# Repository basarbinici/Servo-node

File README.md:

# Servo-node
Isolated PWM generator from CAN

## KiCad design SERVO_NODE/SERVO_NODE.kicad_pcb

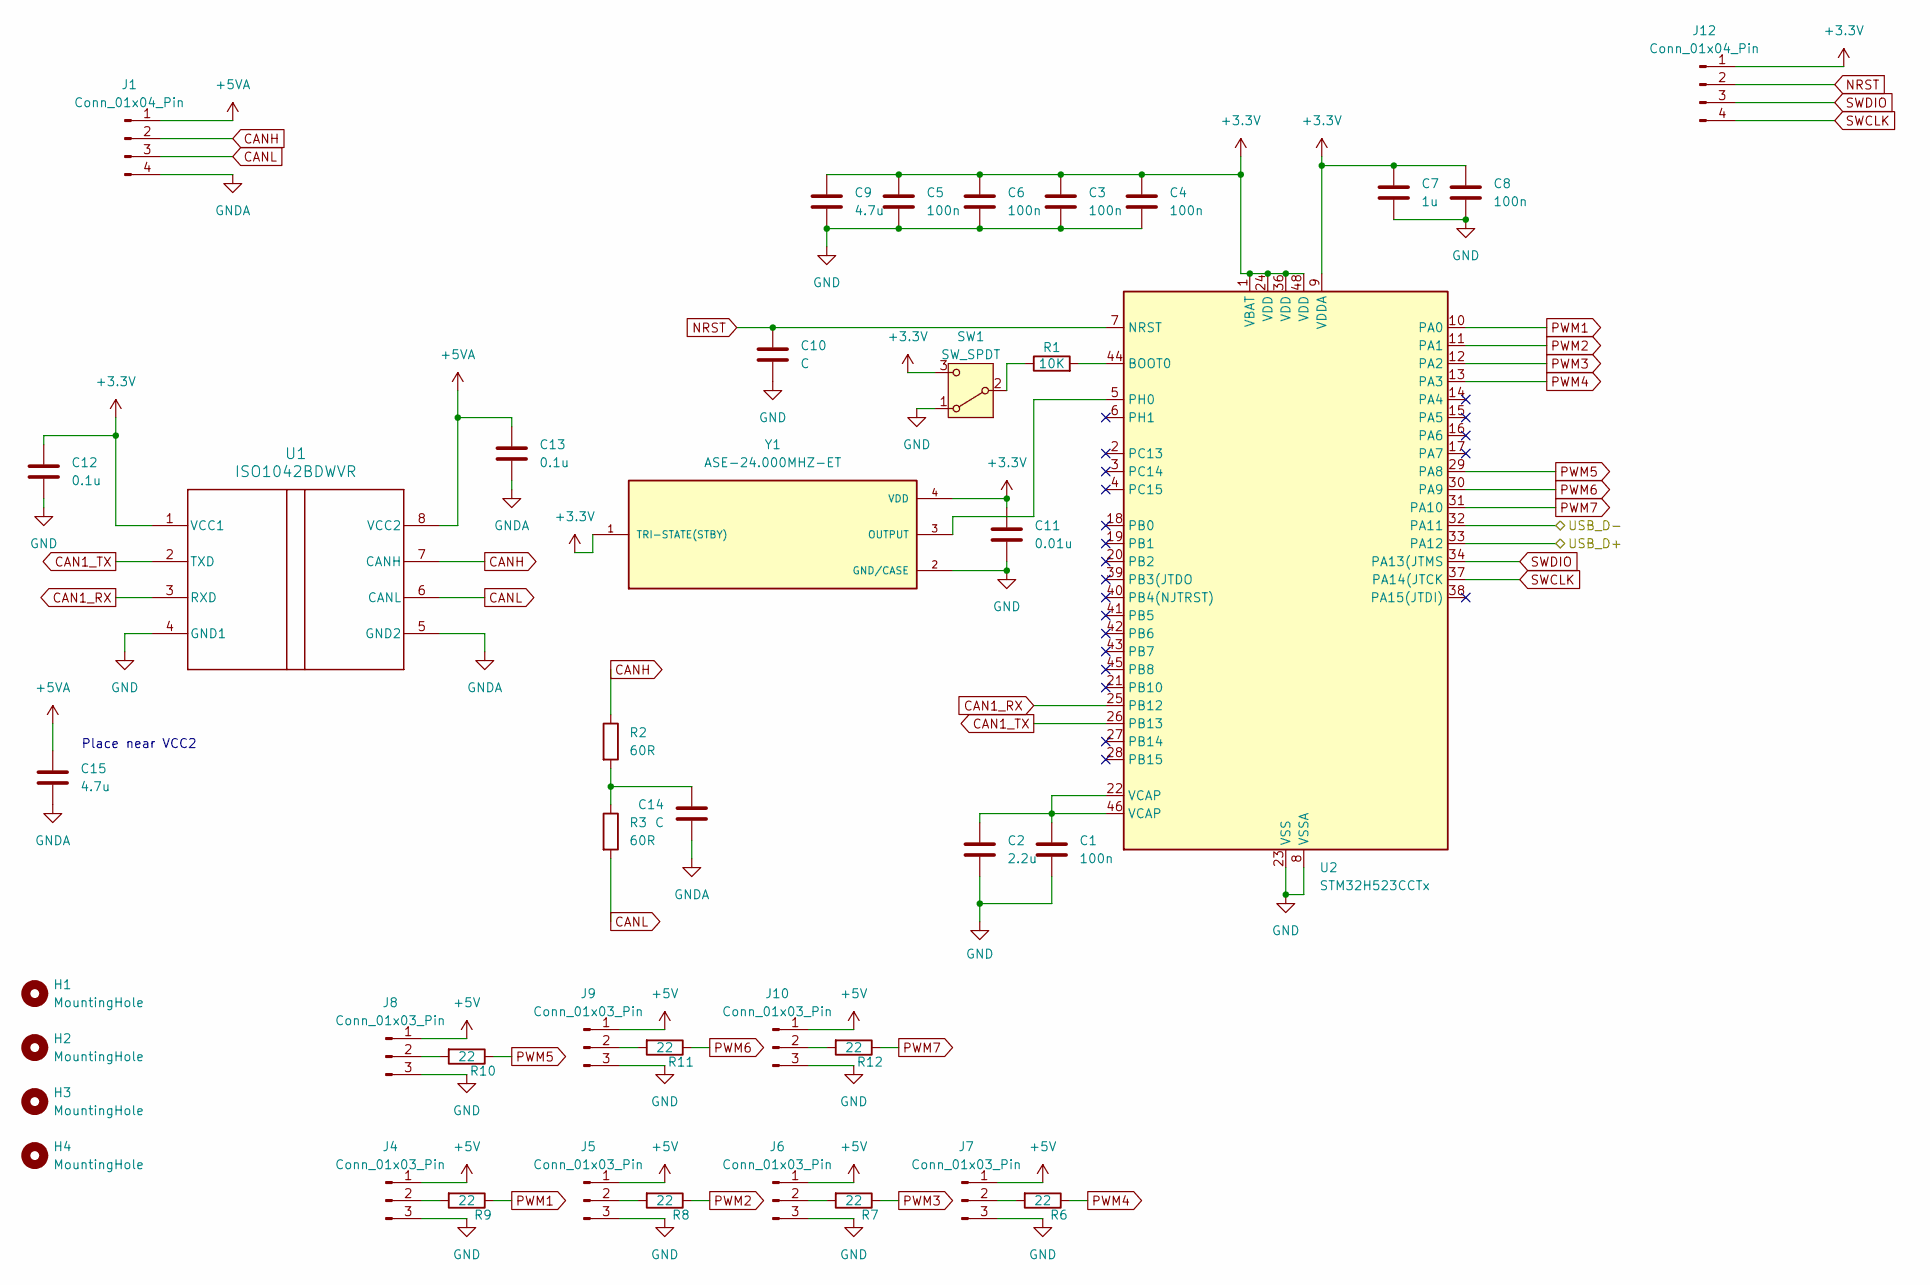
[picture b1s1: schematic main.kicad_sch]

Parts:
C1, C3, C4, C5, C6, C8: 100n; C_0805_2012Metric_Pad1.18x1.45mm_HandSolder
C2: 2.2u; C_0805_2012Metric_Pad1.18x1.45mm_HandSolder
C7: 1u; C_0805_2012Metric_Pad1.18x1.45mm_HandSolder
C9, C15: 4.7u; C_0805_2012Metric_Pad1.18x1.45mm_HandSolder
C10, C14: C; C_0805_2012Metric_Pad1.18x1.45mm_HandSolder
C11: 0.01u; C_0805_2012Metric_Pad1.18x1.45mm_HandSolder
C12, C13: 0.1u; C_0805_2012Metric_Pad1.18x1.45mm_HandSolder
H1, H2, H3, H4: MountingHole; MountingHole_2.2mm_M2_DIN965_Pad
J1: Conn_01x04_Pin; JST_GH_BM04B-GHS-TBT_1x04-1MP_P1.25mm_Vertical
J4, J5, J6, J7, J8, J9, J10: Conn_01x03_Pin; JST_GH_BM03B-GHS-TBT_1x03-1MP_P1.25mm_Vertical
J12: Conn_01x04_Pin; PinHeader_1x04_P2.54mm_Vertical
R1: 10K; R_0805_2012Metric_Pad1.20x1.40mm_HandSolder
R2, R3: 60R; R_0805_2012Metric_Pad1.20x1.40mm_HandSolder
R6, R7, R8, R9, R10, R11, R12: 22; R_0805_2012Metric_Pad1.20x1.40mm_HandSolder
SW1: SW_SPDT; SW_OS102011MS2QN1
U1: ISO1042BDWVR; DWV0008A
U2: STM32H523CCTx; LQFP-48_7x7mm_P0.5mm
Y1: ASE-24.000MHZ-ET; XTAL_ASE-24.000MHZ-ET; PARTREV 02-18-22

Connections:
+3.3V: C3.1, C4.1, C5.1, C6.1, C7.1, C8.1, C9.1, C11.1, C12.1, J12.1, SW1.3 (C), U1.1 (VCC1), U2.1 (VBAT), U2.9 (VDDA), U2.24 (VDD), U2.36 (VDD), U2.48 (VDD), Y1.1 (TRI-STATE(STBY)), Y1.4 (VDD); also elsewhere on the board
+5V: J4.1, J5.1, J6.1, J7.1, J8.1, J9.1, J10.1; also elsewhere on the board
+5VA: C13.1, C15.1, J1.1, U1.8 (VCC2)
/POWER/USB_D+: U2.33 (PA12); also elsewhere on the board
/POWER/USB_D-: U2.32 (PA11); also elsewhere on the board
CAN1_RX: U1.3 (RXD), U2.25 (PB12)
CAN1_TX: U1.2 (TXD), U2.26 (PB13)
CANH: J1.2, R2.1, U1.7 (CANH)
CANL: J1.3, R3.2, U1.6 (CANL)
GND: C1.2, C2.2, C3.2, C4.2, C5.2, C6.2, C7.2, C8.2, C9.2, C10.2, C11.2, C12.2, J4.3, J5.3, J6.3, J7.3, J8.3, J9.3, J10.3, SW1.1 (A), U1.4 (GND1), U2.8 (VSSA), U2.23 (VSS), U2.35 (VSS), U2.47 (VSS), Y1.2 (GND/CASE); also elsewhere on the board
GNDA: C13.2, C14.2, C15.2, J1.4, U1.5 (GND2)
NRST: C10.1, J12.2, U2.7 (NRST)
unnamed: C1.1, C2.1, U2.22 (VCAP), U2.46 (VCAP)
unnamed: C14.1, R2.2, R3.1
unnamed: J4.2, R9.2
unnamed: J5.2, R8.2
unnamed: J6.2, R7.2
unnamed: J7.2, R6.2
unnamed: J8.2, R10.2
unnamed: J9.2, R11.2
unnamed: J10.2, R12.2
unnamed: R1.1, SW1.2 (B)
unnamed: R1.2, U2.44 (BOOT0)
unnamed: U2.5 (PH0), Y1.3 (OUTPUT)
PWM1: R9.1, U2.10 (PA0)
PWM2: R8.1, U2.11 (PA1)
PWM3: R7.1, U2.12 (PA2)
PWM4: R6.1, U2.13 (PA3)
PWM5: R10.1, U2.29 (PA8)
PWM6: R11.1, U2.30 (PA9)
PWM7: R12.1, U2.31 (PA10)
SWCLK: J12.4, U2.37 (PA14(JTCK)
SWDIO: J12.3, U2.34 (PA13(JTMS)

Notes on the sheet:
Place near VCC2

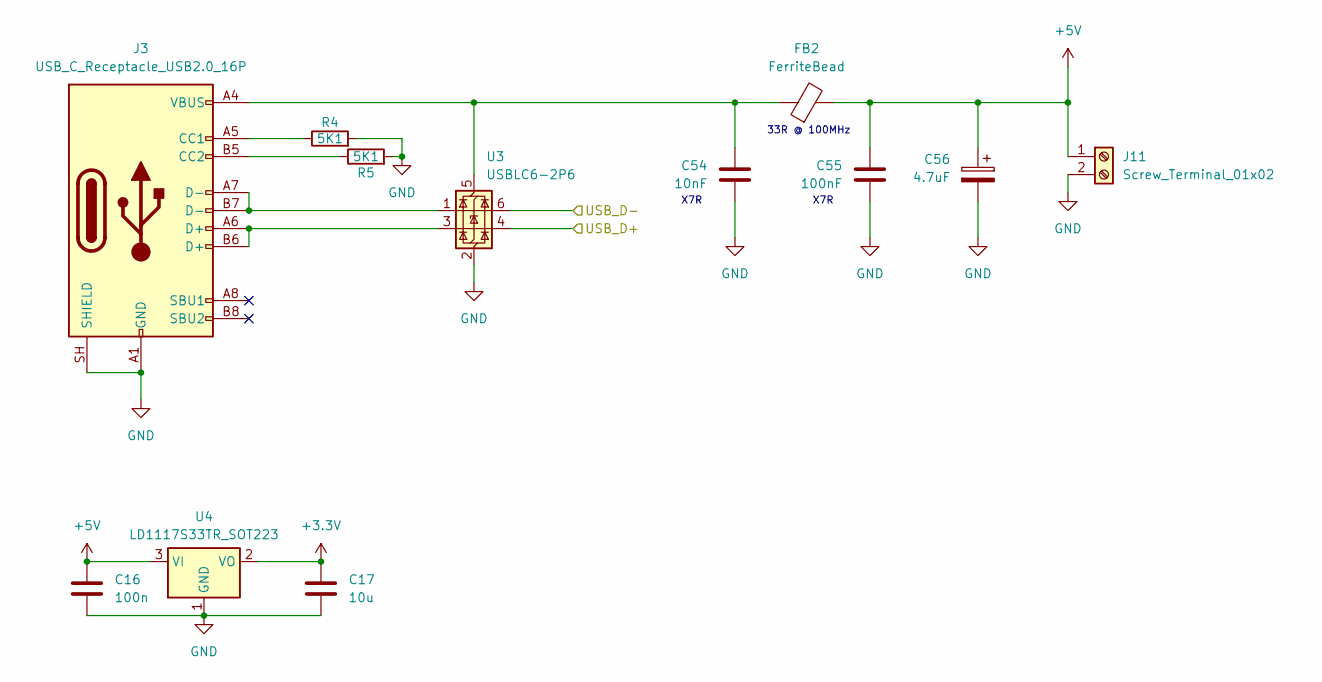
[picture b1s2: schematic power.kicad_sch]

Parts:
C16: 100n; C_0805_2012Metric_Pad1.18x1.45mm_HandSolder
C17: 10u; C_0805_2012Metric_Pad1.18x1.45mm_HandSolder
C54: 10nF; C_0805_2012Metric_Pad1.18x1.45mm_HandSolder
C55: 100nF; C_0805_2012Metric_Pad1.18x1.45mm_HandSolder
C56: 4.7uF; CP_Radial_D4.0mm_P2.00mm
FB2: FerriteBead; L_1206_3216Metric_Pad1.22x1.90mm_HandSolder
J3: USB_C_Receptacle_USB2.0_16P; USB_C_Receptacle_G-Switch_GT-USB-7010ASV
J11: Screw_Terminal_01x02; PhoenixContact_MC_1,5_2-G-5.08_1x02_P5.08mm_Horizontal
R4, R5: 5K1; R_0805_2012Metric_Pad1.20x1.40mm_HandSolder
U3: USBLC6-2P6; SOT-666
U4: LD1117S33TR_SOT223; SOT-223-3_TabPin2

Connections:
+3.3V: C17.1, U4.2 (VO); also elsewhere on the board
+5V: C16.1, C55.1, C56.1, FB2.2, J11.1, U4.3 (VI); also elsewhere on the board
/POWER/USB_D+: U3.4 (I/O2); also elsewhere on the board
/POWER/USB_D-: U3.6 (I/O1); also elsewhere on the board
GND: C16.2, C17.2, C54.2, C55.2, C56.2, J3.A1 (GND), J3.A12 (GND), J3.B1 (GND), J3.B12 (GND), J3.SH (SHIELD), J11.2, R4.2, R5.2, U3.2 (GND), U4.1 (GND); also elsewhere on the board
unnamed: J3.A5 (CC1), R4.1
unnamed: J3.B5 (CC2), R5.1
unnamed: J3.A6 (D+), J3.B6 (D+), U3.3 (I/O2)
unnamed: J3.A7 (D-), J3.B7 (D-), U3.1 (I/O1)
unnamed: C54.1, FB2.1, J3.A4 (VBUS), J3.A9 (VBUS), J3.B4 (VBUS), J3.B9 (VBUS), U3.5 (VBUS)

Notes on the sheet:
X7R
33R @ 100MHz

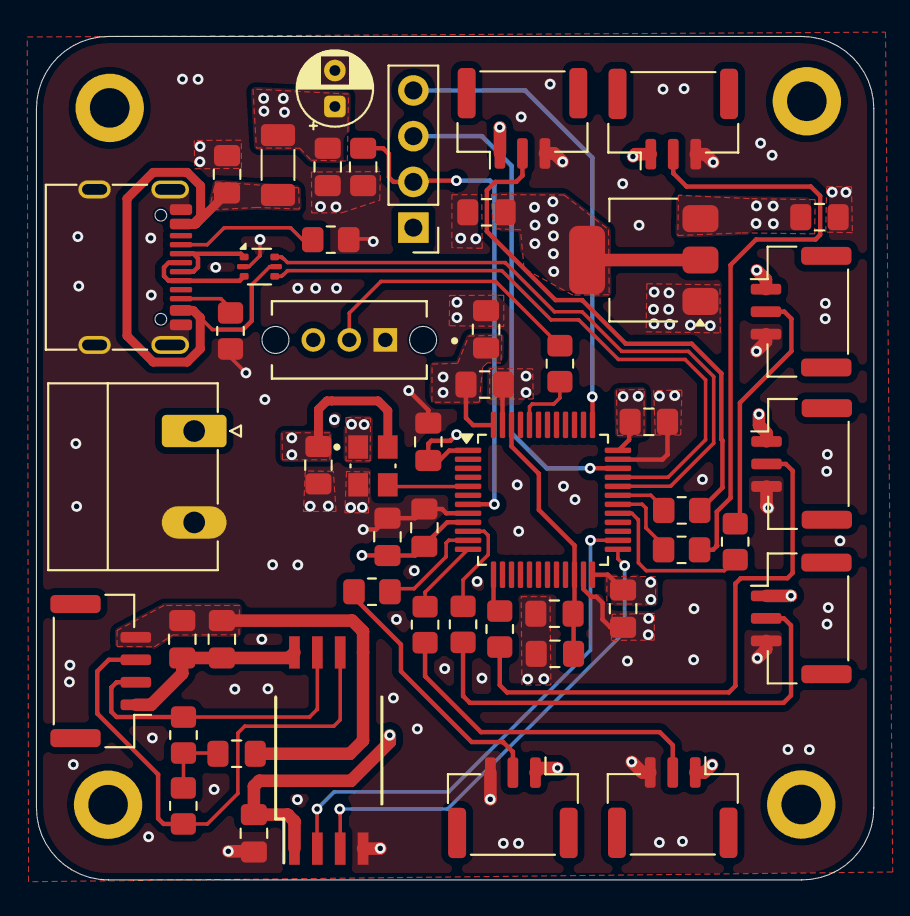
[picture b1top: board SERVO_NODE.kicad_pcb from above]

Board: 4 copper layers, 46.5 x 46.9 mm, 54 parts (0 on the bottom side), 38 nets.
